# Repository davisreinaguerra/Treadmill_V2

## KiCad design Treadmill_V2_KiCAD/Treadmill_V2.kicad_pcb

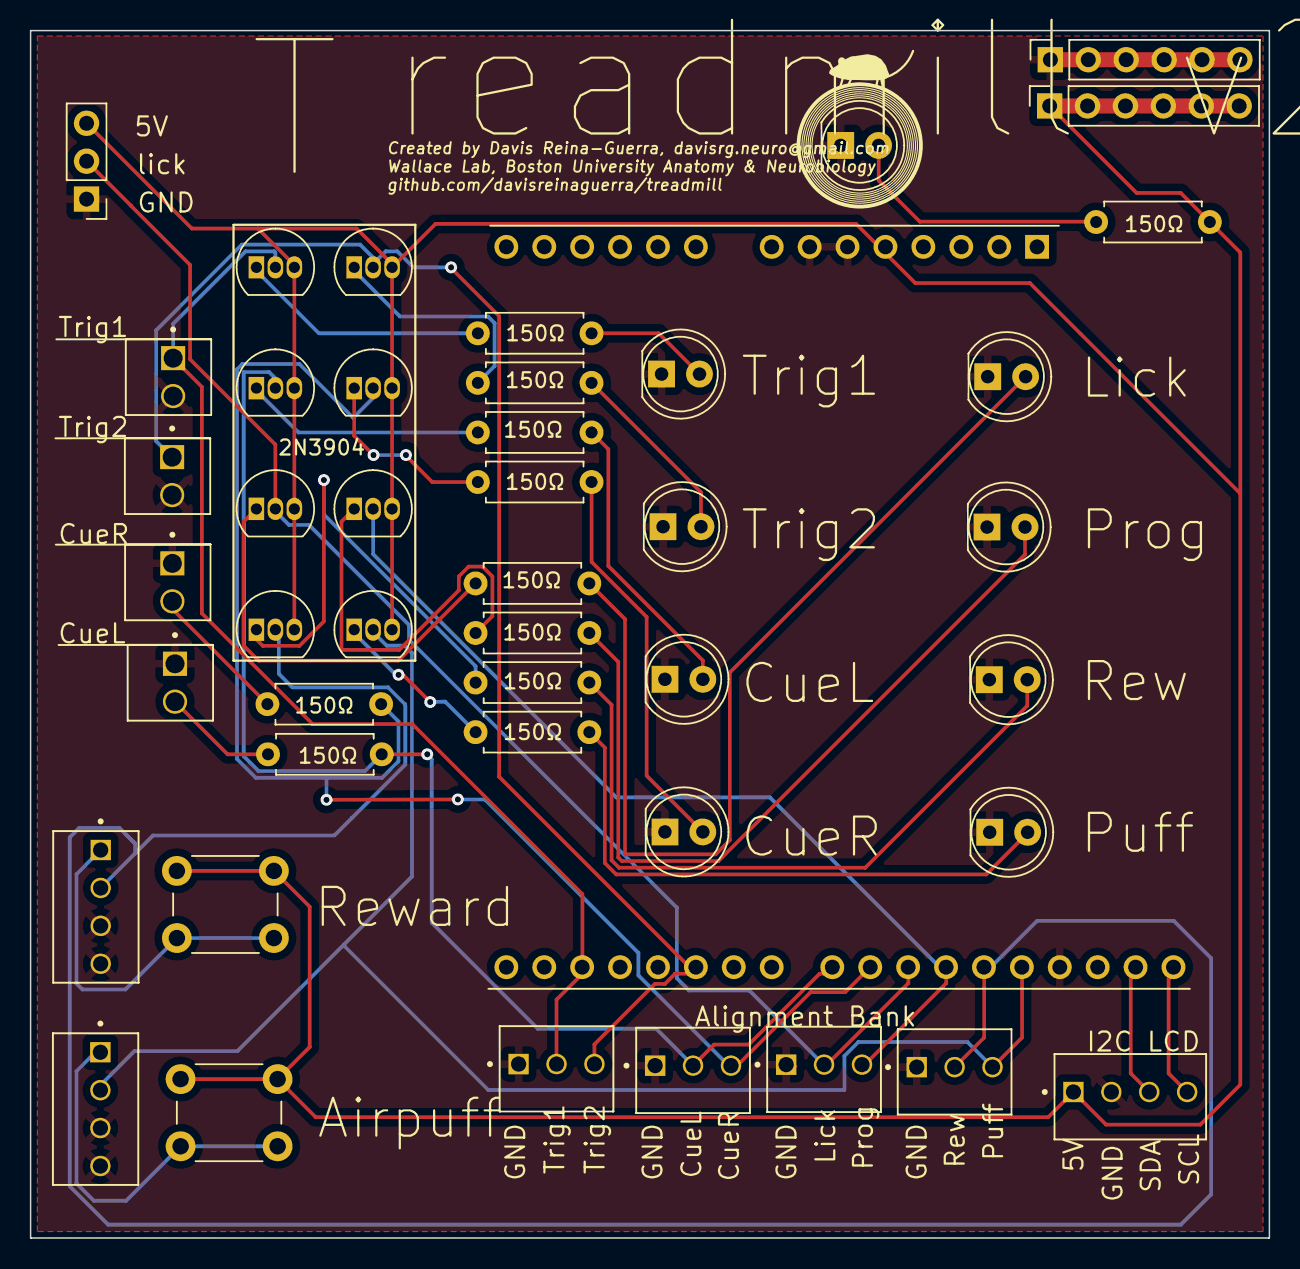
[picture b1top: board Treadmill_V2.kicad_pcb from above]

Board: 2 copper layers, 83.0 x 80.9 mm, 43 parts (0 on the bottom side), 33 nets.

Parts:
A1: Arduino_UNO_R3
A2, A3, A4, A5: Alignment; TE_640456-3
D1, D2: LED: blue; TE_640454-2
D3, D4, D5, D6, D7, D8, D9, D10: LED: white; LED_D5.0mm
D11: LED: blue; LED_D5.0mm
I2C_LCD1: Main; TE_640456-4
Q1, Q2, Q3, Q4, Q5, Q6, Q7, Q8: 2N3904; TO-92_Inline
R1, R2, R3, R4, R5, R6, R7, R8, R9, R10, R11: 150Ω; R_Axial_DIN0207_L6.3mm_D2.5mm_P7.62mm_Horizontal
SAirpuff1: TE_640456-4
SReward1: TE_640456-4
SWAirpuff1: SW_Push; SW_PUSH_6mm
SWReward1: SW_Push; SW_PUSH_6mm
TLick1: PinHeader_1x03_P2.54mm_Vertical
trig1, trig2: TE_640454-2

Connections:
/5V: A1.5 (+5V), I2C_LCD1.1 (5V), Q1.3 (C), Q2.3 (C), Q3.3 (C), Q4.3 (C), Q5.3 (C), Q6.3 (C), Q7.3 (C), Q8.3 (C), R11.2, SWAirpuff1.1, SWReward1.1, TLick1.3 (5V)
/GND: A1.6 (GND), A1.7 (GND), A1.29 (GND), A2.1 (GND), A3.1 (GND), A4.1 (GND), A5.1 (GND), D1.1 (K), D2.1 (K), D3.1 (K), D4.1 (K), D5.1 (K), D6.1 (K), D7.1 (K), D8.1 (K), D9.1 (K), D10.1 (K), D11.1 (K), I2C_LCD1.2 (GND), SAirpuff1.3 (GND), SAirpuff1.4 (GND), SReward1.3 (GND), SReward1.4 (GND), TLick1.1 (GND), trig1.2 (GND), trig2.2 (GND)
/SCL: A1.32 (SCL/A5), I2C_LCD1.4 (SCL)
/SDA: A1.31 (SDA/A4), I2C_LCD1.3 (SDA)
/airpuff: A1.28 (D13), A5.3 (Align), Q8.2 (B), SAirpuff1.2 (TRIG)
/cueL: A1.23 (D8), A3.2 (Align), Q3.2 (B), R1.2
/cueR: A1.24 (D9), A3.3 (Align), Q4.2 (B), R2.2
/lick: A1.25 (D10), A4.2 (Align), Q5.2 (B), TLick1.2 (Sig)
/prog: A1.26 (D11), A4.3 (Align), Q6.2 (B)
/reward: A1.27 (D12), A5.2 (Align), Q7.2 (B), SReward1.2 (TRIG)
/trig1: A1.17 (D2), A2.2 (Align), Q1.2 (B), trig1.1 (OUT)
/trig2: A1.20 (D5), A2.3 (Align), Q2.2 (B), trig2.1 (OUT)
unnamed: D1.2 (A), R1.1
unnamed: D2.2 (A), R2.1
unnamed: D3.2 (A), R3.1
unnamed: D4.2 (A), R4.1
unnamed: D5.2 (A), R5.1
unnamed: D6.2 (A), R6.1
unnamed: D7.2 (A), R7.1
unnamed: D8.2 (A), R8.1
unnamed: D9.2 (A), R9.1
unnamed: D10.2 (A), R10.1
unnamed: D11.2 (A), R11.1
unnamed: Q1.1 (E), R3.2
unnamed: Q2.1 (E), R4.2
unnamed: Q3.1 (E), R5.2
unnamed: Q4.1 (E), R6.2
unnamed: Q5.1 (E), R7.2
unnamed: Q6.1 (E), R8.2
unnamed: Q7.1 (E), R9.2
unnamed: Q8.1 (E), R10.2
unnamed: SAirpuff1.1 (TRIG), SWAirpuff1.2
unnamed: SReward1.1 (TRIG), SWReward1.2

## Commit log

2024-11-21 Create delete
2025-03-29 Rename new.mat to new run.mat
